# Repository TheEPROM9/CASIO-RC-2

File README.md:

# CASIO-RC-2
This RAM pack is for the CASIO FX-720P or similar pocket computer. This unit is 2KB 4-BIT memory with battery backup that is user removable. The RAM pack also came in 4KB variants, I do not have one of these yet. This will be an open source project as mod & contribute as you desire.

I have now uploaded the full schmatic & PCB files. As usual they are currently untesdted to feel free to contribute.

Link to project: [CASIO RC-2 RAM Pack](https://www.theeprom9.co.uk/vintage-computers/reverse-engineering-computers/casio-rc-2-ram-pack)

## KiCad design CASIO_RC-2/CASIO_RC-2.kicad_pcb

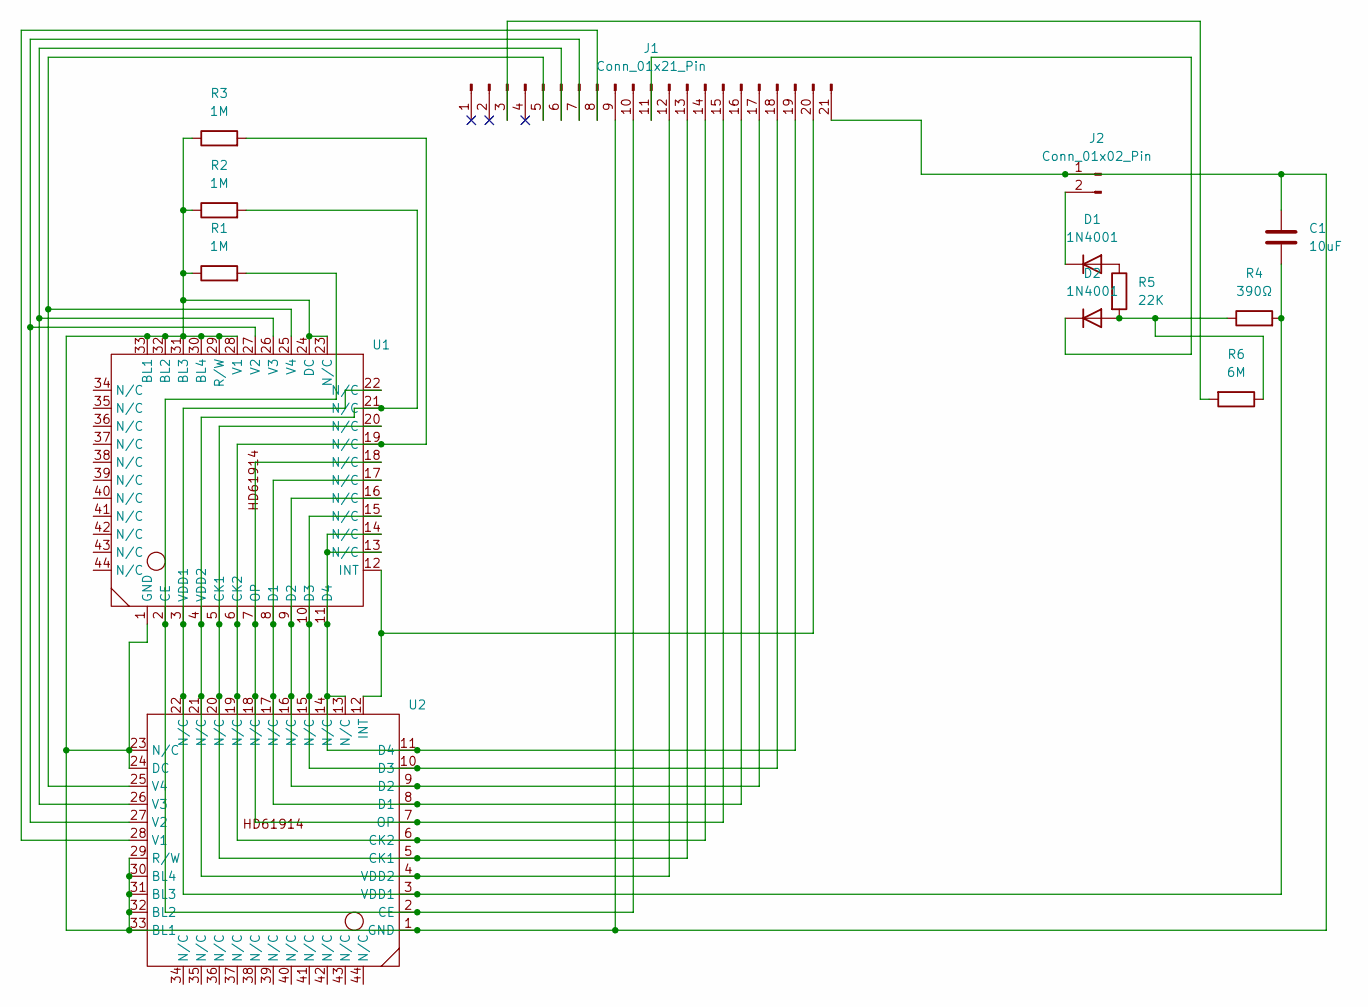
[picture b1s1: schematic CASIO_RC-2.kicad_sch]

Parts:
C1: 10uF; C_1808_4520Metric
D1, D2: 1N4001; D_1206_3216Metric
J1: Conn_01x21_Pin; CASIO_RC-2_RAM_Pinheadder
J2: Conn_01x02_Pin; CR2023_Battery_Terminal
R1, R2, R3: 1M; R_1206_3216Metric
R4: 390Ω; R_1206_3216Metric
R5: 22K; R_1206_3216Metric
R6: 6M; R_1206_3216Metric
U1, U2: HD61914

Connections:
unnamed: D1.2 (A), R5.1
unnamed: D1.1 (K), J2.2
unnamed: D2.2 (A), R4.1, R5.2, R6.1
unnamed: D2.1 (K), J1.11
unnamed: J1.3, R6.2
unnamed: J1.5, U1.25 (V4), U2.25 (V4)
unnamed: J1.6, U1.26 (V3), U2.26 (V3)
unnamed: J1.7, U1.27 (V2), U2.27 (V2)
unnamed: J1.8, U2.28 (V1)
unnamed: J1.10, R1.2, U1.2 (CE), U2.2 (CE)
unnamed: J1.12, R2.2, U1.4 (VDD2), U1.21 (N/C), U2.4 (VDD2), U2.21 (N/C)
unnamed: J1.13, U1.5 (CK1), U1.20 (N/C), U2.5 (CK1), U2.20 (N/C)
unnamed: J1.14, R3.2, U1.6 (CK2), U1.19 (N/C), U2.6 (CK2), U2.19 (N/C)
unnamed: J1.15, U1.7 (OP), U1.18 (N/C), U2.7 (OP), U2.18 (N/C)
unnamed: J1.16, U1.8 (D1), U1.17 (N/C), U2.8 (D1), U2.17 (N/C)
unnamed: J1.17, U1.9 (D2), U1.16 (N/C), U2.9 (D2), U2.16 (N/C)
unnamed: J1.18, U1.10 (D3), U1.15 (N/C), U2.10 (D3), U2.15 (N/C)
unnamed: J1.19, U1.11 (D4), U1.13 (N/C), U1.14 (N/C), U2.11 (D4), U2.13 (N/C), U2.14 (N/C)
unnamed: J1.20, U1.12 (INT), U2.12 (INT)
unnamed: C1.1, J1.9, J1.21, J2.1, R1.1, R2.1, R3.1, U1.1 (GND), U1.23 (N/C), U1.24 (DC), U1.28 (V1), U1.29 (R/W), U1.30 (BL4), U1.31 (BL3), U1.32 (BL2), U1.33 (BL1), U2.1 (GND), U2.23 (N/C), U2.24 (DC), U2.29 (R/W), U2.30 (BL4), U2.31 (BL3), U2.32 (BL2), U2.33 (BL1)
unnamed: C1.2, R4.2, U1.3 (VDD1), U1.22 (N/C), U2.3 (VDD1), U2.22 (N/C)

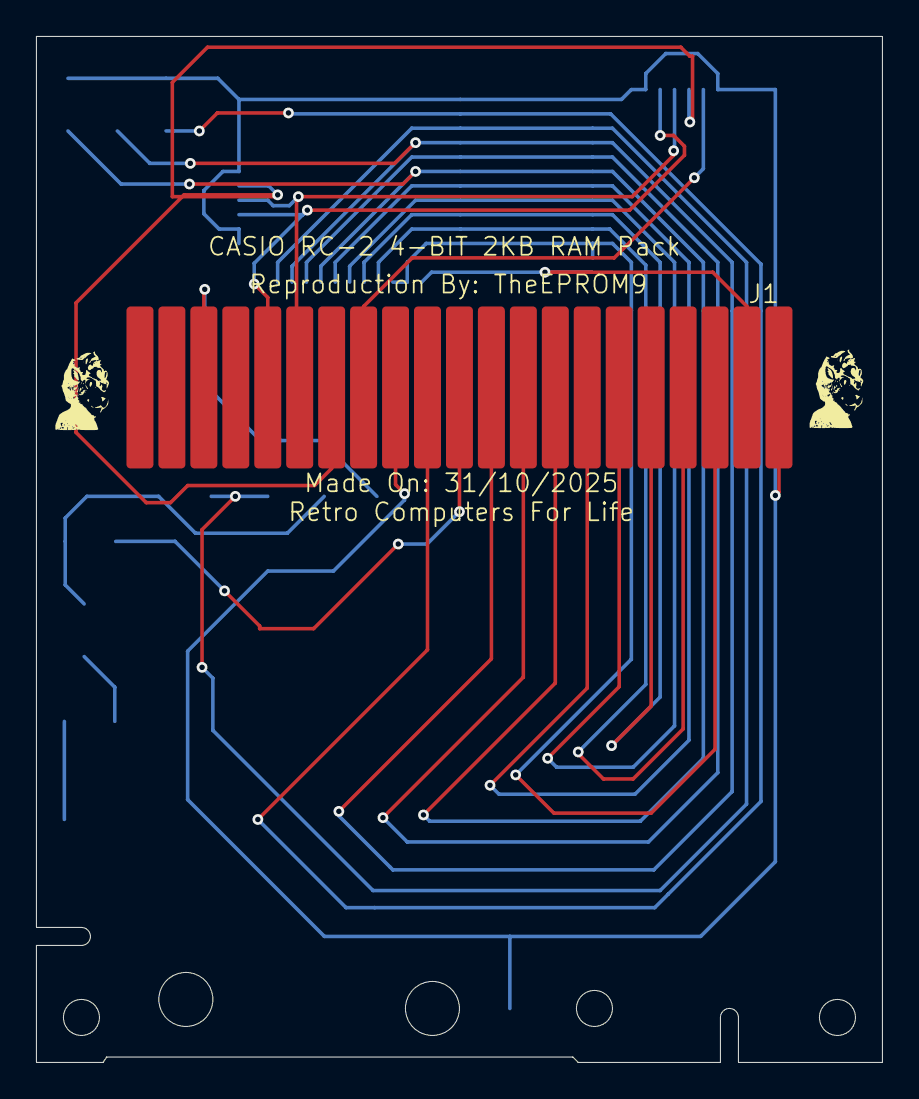
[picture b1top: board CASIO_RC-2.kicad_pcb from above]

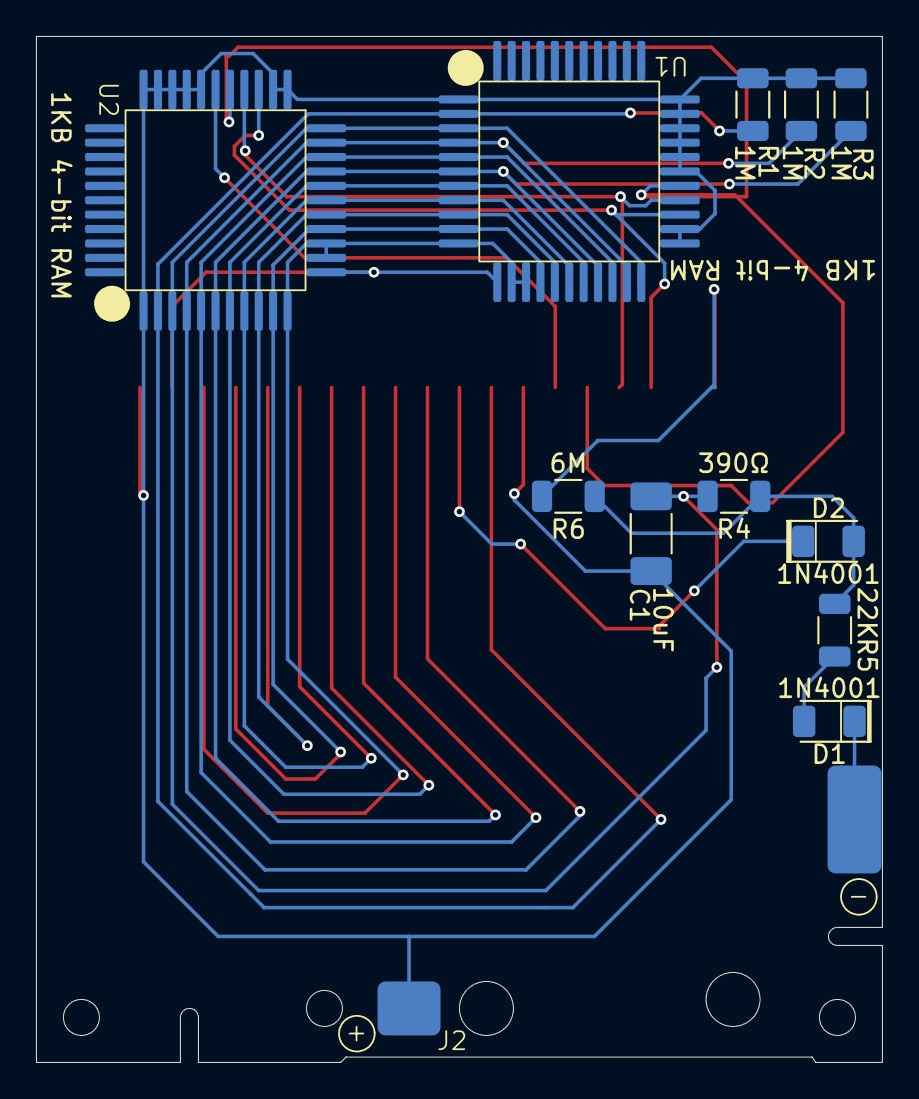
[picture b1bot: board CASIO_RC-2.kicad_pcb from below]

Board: 2 copper layers, 47.0 x 57.0 mm, 13 parts (12 on the bottom side), 21 nets.

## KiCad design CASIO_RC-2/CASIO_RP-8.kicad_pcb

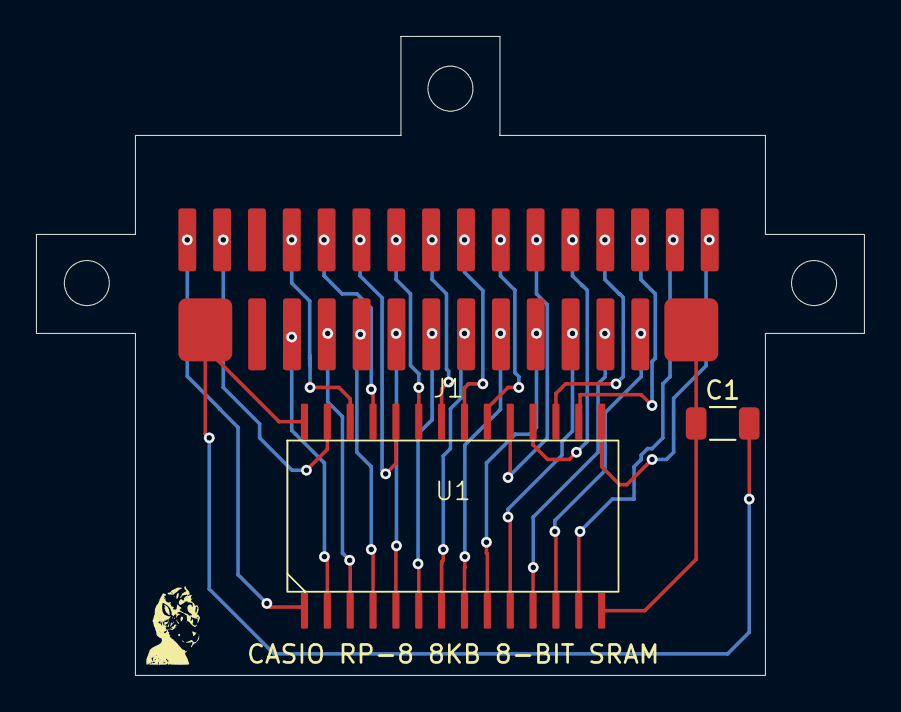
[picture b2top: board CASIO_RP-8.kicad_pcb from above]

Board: 2 copper layers, 46.0 x 35.5 mm, 3 parts (0 on the bottom side), 28 nets.

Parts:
C1: 10uF; C_1206_3216Metric
J1: CASIO_RP-8_16_Pin_Headder
U1: LC3564PML

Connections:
unnamed: J1.27, U1.10 (A0)
unnamed: J1.26, U1.9 (A1)
unnamed: J1.25, U1.8 (A2)
unnamed: J1.24, U1.7 (A3)
unnamed: J1.23, U1.6 (A4)
unnamed: J1.22, U1.5 (A5)
unnamed: J1.21, U1.4 (A6)
unnamed: J1.20, U1.3 (A7)
unnamed: J1.5, U1.25 (A8)
unnamed: J1.6, U1.24 (A9)
unnamed: J1.9, U1.21 (A10)
unnamed: J1.7, U1.23 (A11)
unnamed: J1.19, U1.2 (A12)
unnamed: J1.10, U1.20 (CE1)
unnamed: J1.4, U1.26 (CE2)
unnamed: C1.1, J1.30, U1.14 (GND)
unnamed: J1.28, U1.11 (I/O1)
unnamed: J1.29, U1.12 (I/O2)
unnamed: J1.15, U1.13 (I/O3)
unnamed: J1.16, U1.15 (I/O4)
unnamed: J1.14, U1.16 (I/O5)
unnamed: J1.13, U1.17 (I/O6)
unnamed: J1.12, U1.18 (I/O7)
unnamed: J1.11, U1.19 (I/O8)
unnamed: J1.1, U1.1 (NO)
unnamed: J1.8, U1.22 (OE)
unnamed: C1.2, J1.17, U1.28 (VCC)
unnamed: J1.2, U1.27 (WE)

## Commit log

2025-10-16 Update README.md
    Added link to website project page.
2025-10-20 First Upload Of Completed Schematic
2025-10-31 Fix Error With Schematic & Designed PCB
    An error with the schematic where the 6M resistor connected to the wrong side of the diode. I have also finally got round to designing the PCB after a ton of delays due to Migraine's & work burnout.
2025-10-31 Custom Footprints Uploaded
2025-10-31 Updated PCB
    Added all the little PCB details & fixed the hold spacing.
